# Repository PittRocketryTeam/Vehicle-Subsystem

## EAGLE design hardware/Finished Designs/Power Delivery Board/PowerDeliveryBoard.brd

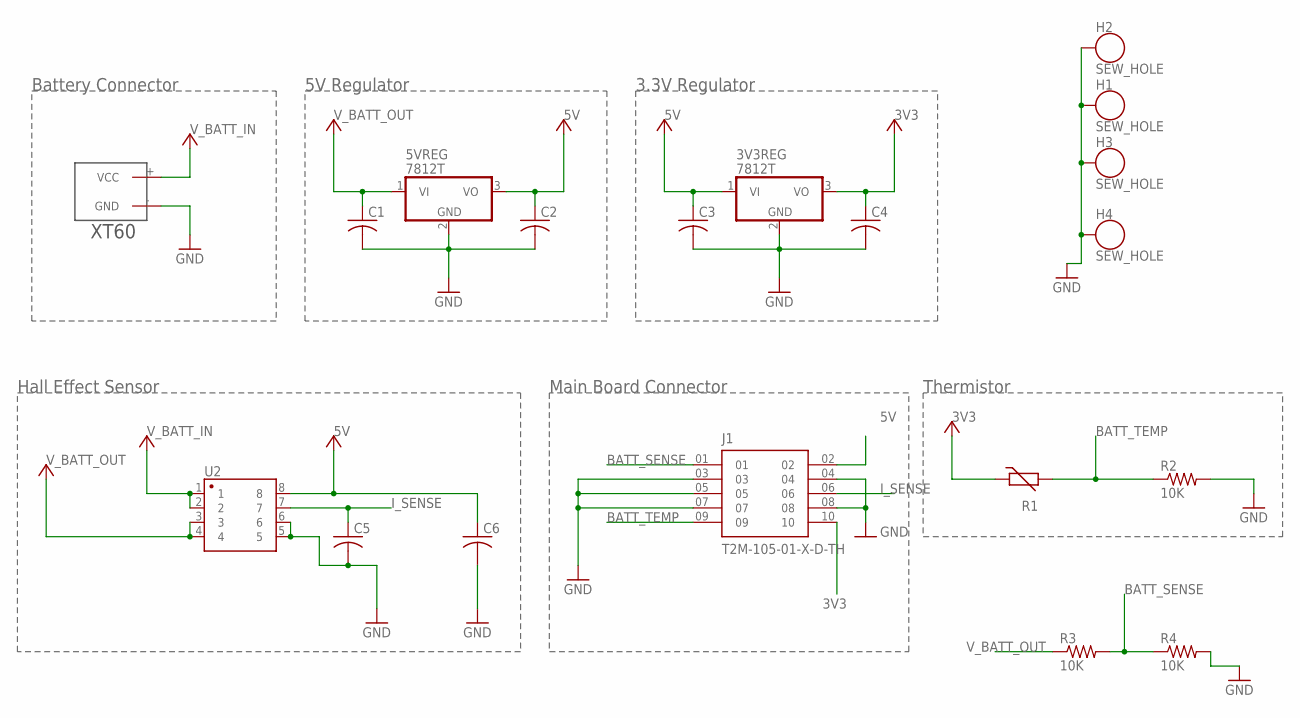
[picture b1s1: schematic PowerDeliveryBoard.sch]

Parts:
3V3REG, 5VREG: 7812T; TO220H
C1, C2, C3, C4, C5, C6: C-USC0805; C0805
H1, H2, H3, H4: SEW_HOLE; SIMPLE_HOLE
J1: T2M-105-01-X-D-TH; SAMTEC_T2M-105-01-X-D-TH
R1: THERMISTOR-5; R-5
R2, R3, R4: 10K; R0805
U2: ASC723; SO08
U$3: XT60_XT60

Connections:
3V3: 3V3REG.3 (VO), C4.1, J1.10, R1.1
5V: 3V3REG.1 (VI), 5VREG.3 (VO), C2.1, C3.1, C6.1, J1.02, U2.8
BATT_SENSE: J1.01, R3.2, R4.1
BATT_TEMP: J1.09, R1.2, R2.1
GND: 3V3REG.2 (GND), 5VREG.2 (GND), C1.2, C2.2, C3.2, C4.2, C5.2, C6.2, H1.P$1, H2.P$1, H3.P$1, H4.P$1, J1.03, J1.04, J1.05, J1.07, J1.08, R2.2, R4.2, U2.5, U2.6, U$3.- (GND)
I_SENSE: C5.1, J1.06, U2.7
V_BATT_IN: U2.1, U2.2, U$3.+ (VCC)
V_BATT_OUT: 5VREG.1 (VI), C1.1, R3.1, U2.3, U2.4

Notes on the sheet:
Hall Effect Sensor
5V Regulator
3.3V Regulator
Thermistor
Battery Connector
Main Board Connector

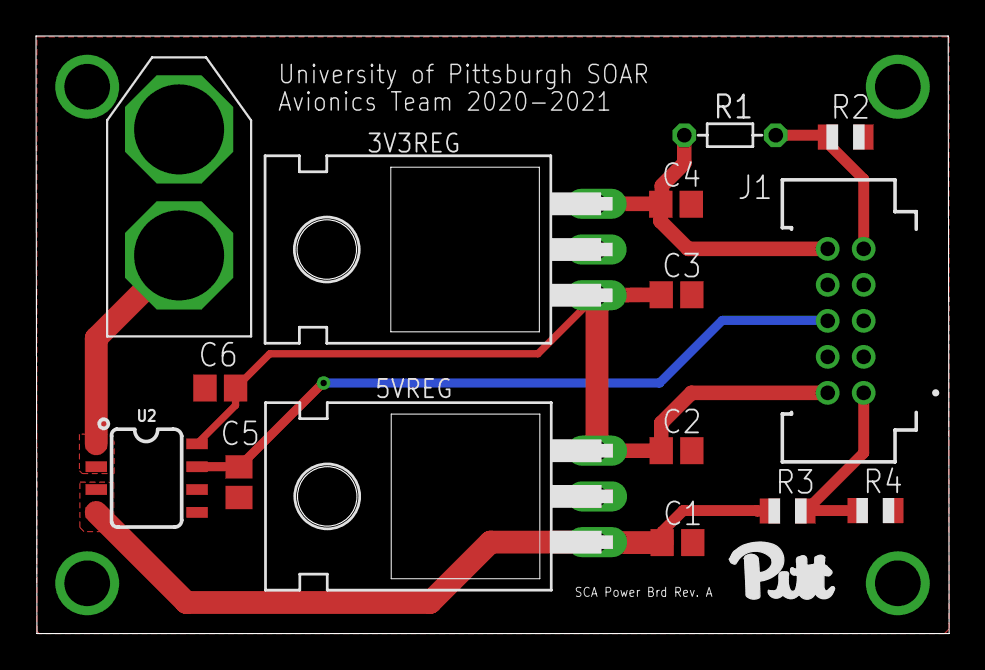
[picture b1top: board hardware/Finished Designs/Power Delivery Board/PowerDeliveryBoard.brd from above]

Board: 2 copper layers, 50.7 x 33.2 mm, 19 parts (0 on the bottom side), 8 nets.

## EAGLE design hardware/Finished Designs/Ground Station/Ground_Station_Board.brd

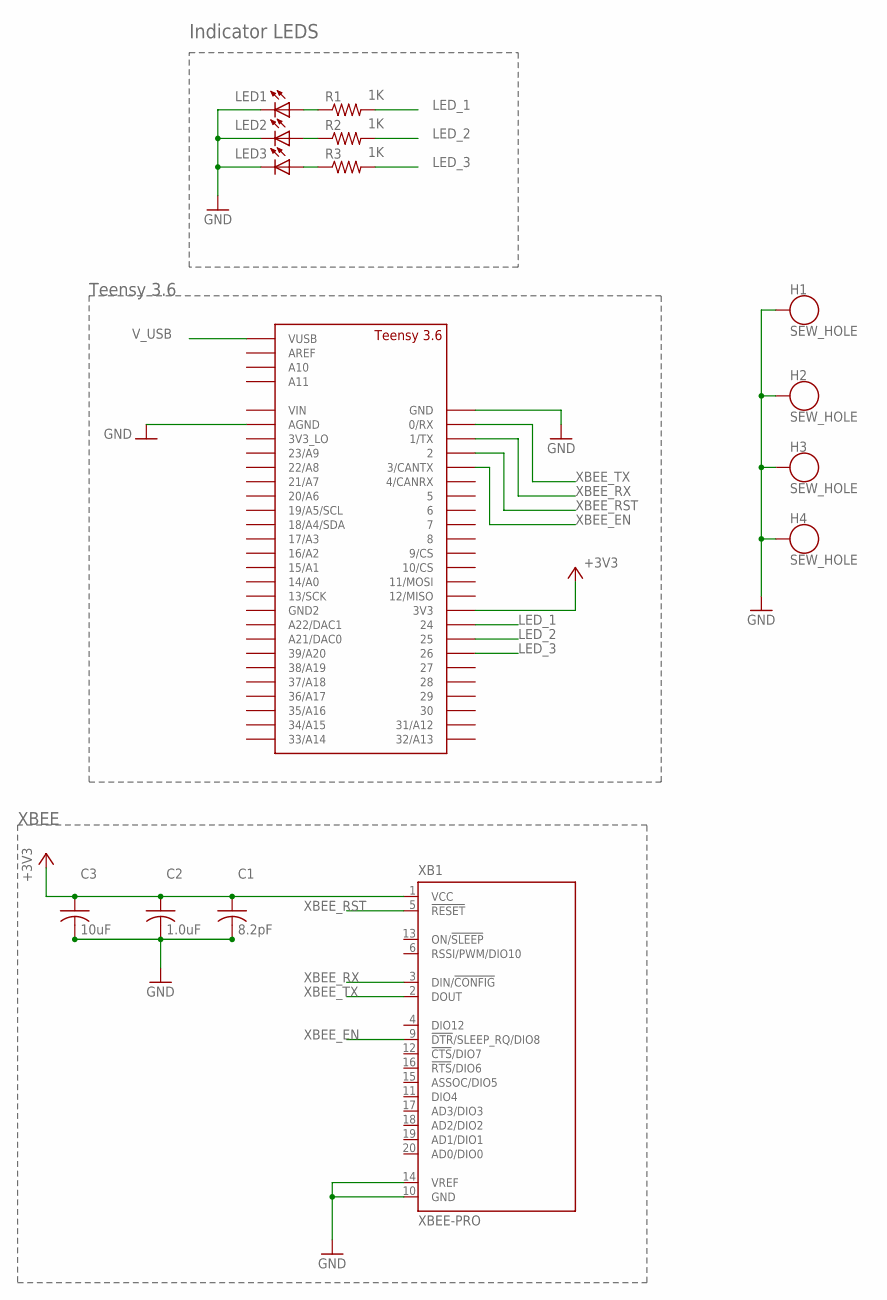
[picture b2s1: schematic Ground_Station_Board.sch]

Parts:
C1: 8.2pF; C025-024X044
C2: 1.0uF; C025-024X044
C3: 10uF; C025-024X044
H1, H2, H3, H4: SEW_HOLE; SIMPLE_HOLE
LED1, LED2, LED3: LED5MM
R1, R2, R3: 1K; 0207/7
U$2: TEENSY_3.5/3.6_BASIC
XB1: XBEE-PRO

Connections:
+3V3: C1.1, C2.1, C3.1, U$2.3V3, XB1.1 (VCC)
GND: C1.2, C2.2, C3.2, H1.P$1, H2.P$1, H3.P$1, H4.P$1, LED1.K (C), LED2.K (C), LED3.K (C), U$2.AGND, U$2.GND, XB1.10 (GND), XB1.14 (VREF)
LED_1: R1.2, U$2.24
LED_2: R2.2, U$2.25
LED_3: R3.2, U$2.26
unnamed: LED1.A, R1.1
unnamed: LED2.A, R2.1
unnamed: LED3.A, R3.1
V_USB: U$2.VUSB
XBEE_EN: U$2.3/CANTX, XB1.9 (!DTR!/SLEEP_RQ/DIO8)
XBEE_RST: U$2.2, XB1.5 (!RESET)
XBEE_RX: U$2.1/TX, XB1.3 (DIN/!CONFIG)
XBEE_TX: U$2.0/RX, XB1.2 (DOUT)

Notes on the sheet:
Indicator LEDS
XBEE
Teensy 3.6

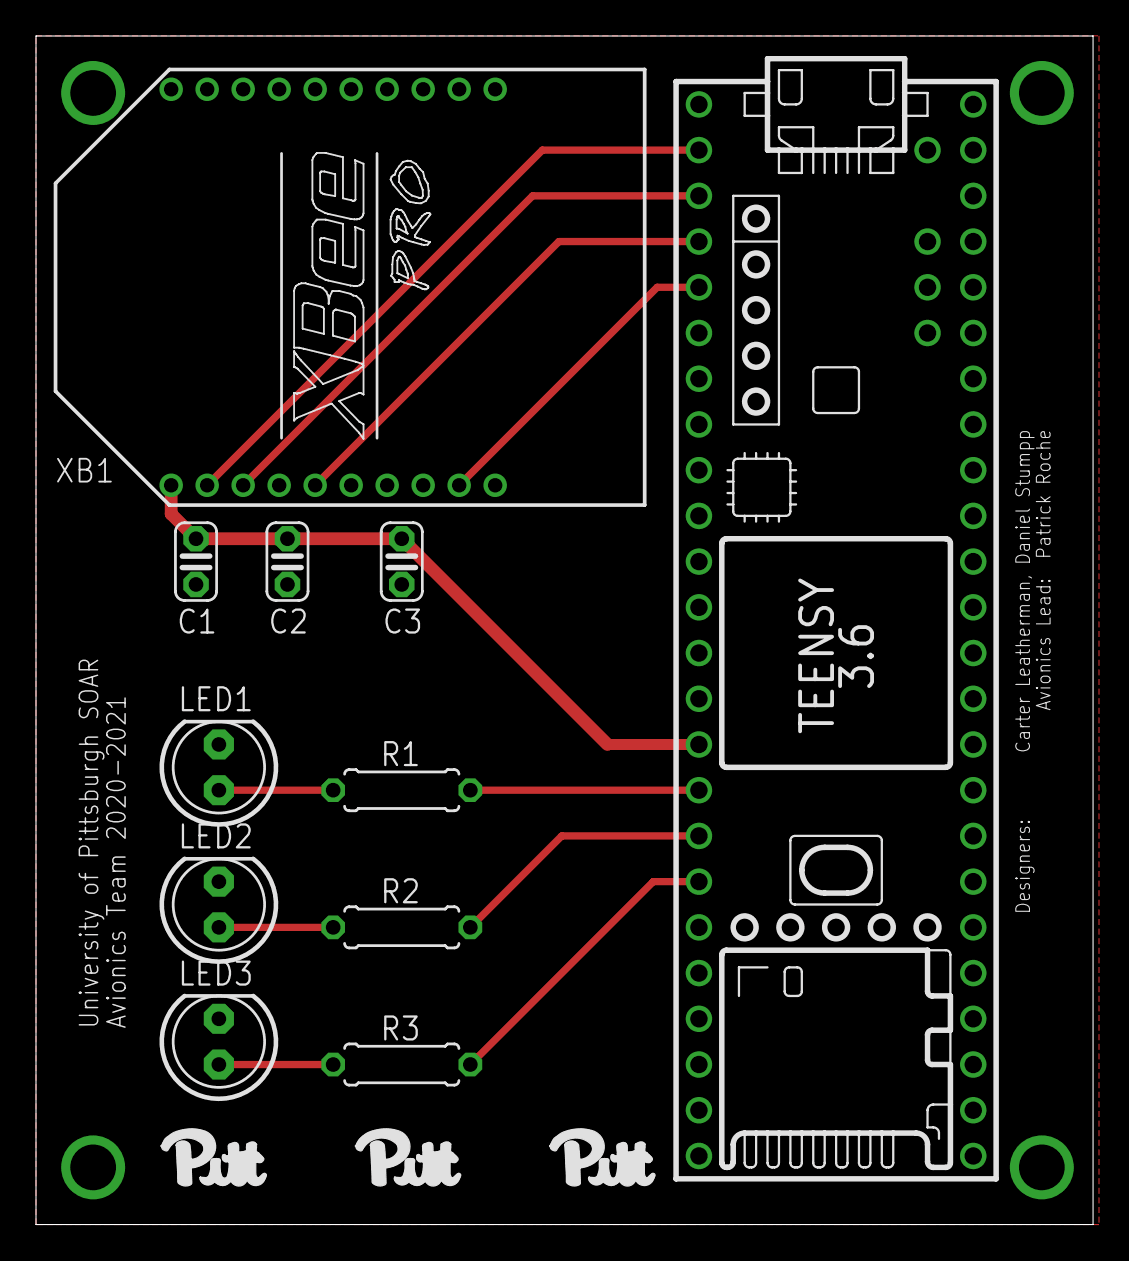
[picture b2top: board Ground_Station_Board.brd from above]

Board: 2 copper layers, 58.7 x 66.0 mm, 15 parts (0 on the bottom side), 12 nets.

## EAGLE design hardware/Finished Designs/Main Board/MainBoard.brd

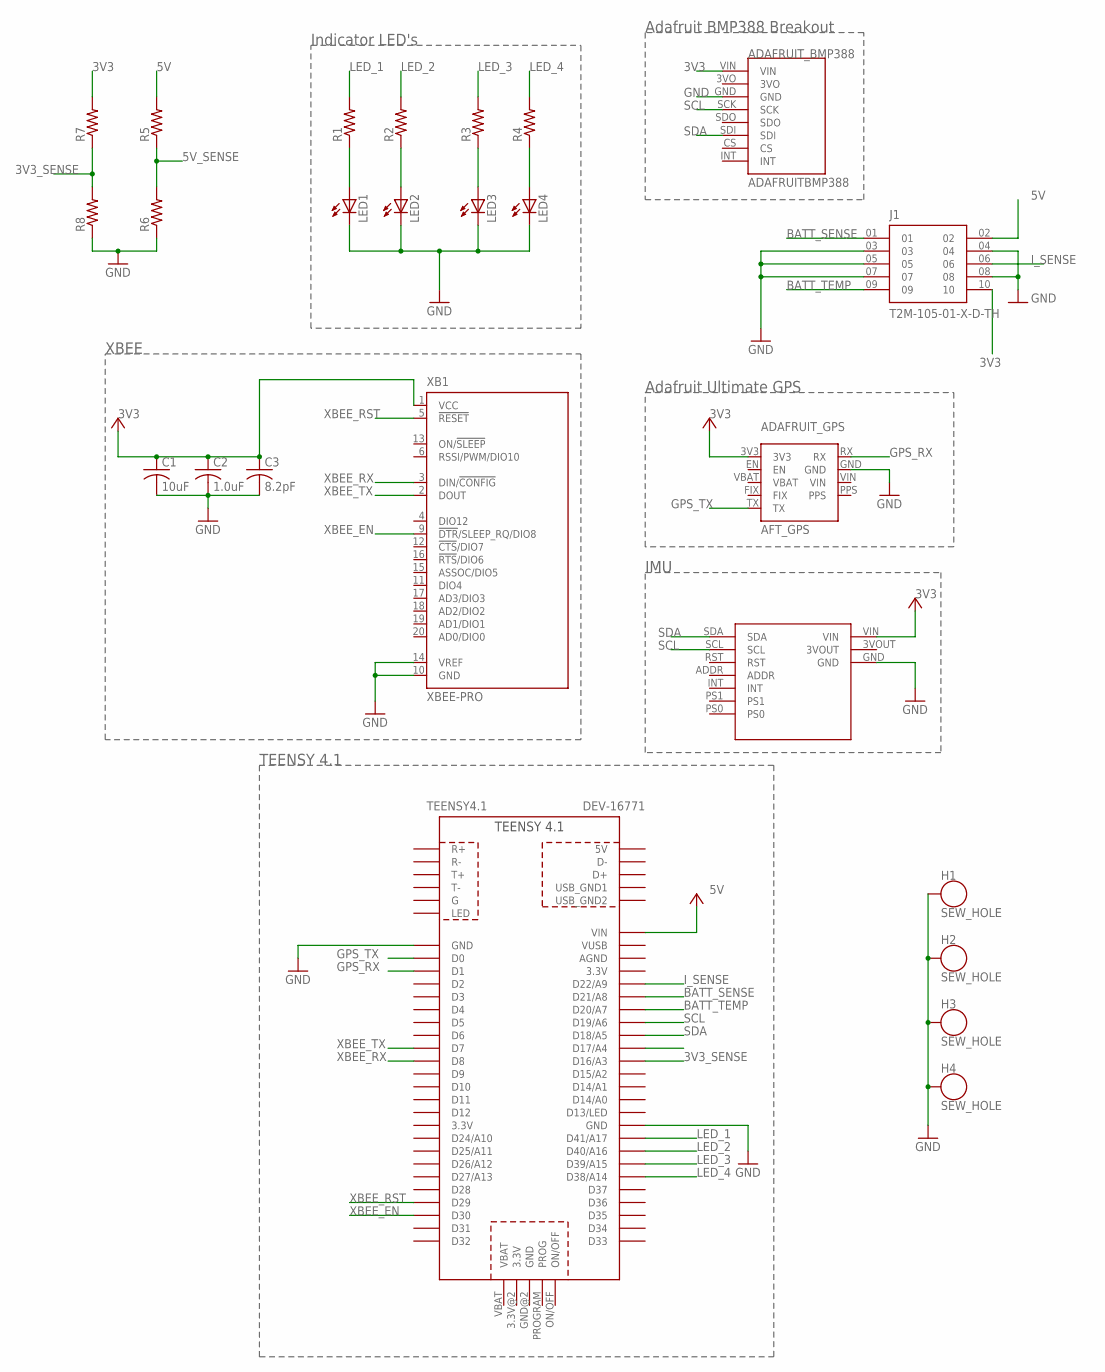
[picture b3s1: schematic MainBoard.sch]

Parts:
ADAFRUIT_BMP388: ADAFRUITBMP388
ADAFRUIT_GPS: AFT_GPS
C1: 10uF; C0805
C2: 1.0uF; C0805
C3: 8.2pF; C0805
H1, H2, H3, H4: SEW_HOLE; SIMPLE_HOLE
J1: T2M-105-01-X-D-TH; SAMTEC_T2M-105-01-X-D-TH
LED1, LED2, LED3, LED4: LED5MM
R1, R2, R3, R4, R5, R6, R7, R8: R-US_R0805; R0805
TEENSY4.1: DEV-16771
U$1: IMU_BREAKOUT; BNO055_BREAKOUT
XB1: XBEE-PRO

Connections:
3.3V: TEENSY4.1.3.3V, TEENSY4.1.3.3V@1 (3.3V), TEENSY4.1.3.3V@2 (3.3V)
3V3: ADAFRUIT_BMP388.VIN, ADAFRUIT_GPS.3V3, C1.1, C2.1, C3.1, J1.10, R7.2, U$1.VIN, XB1.1 (VCC)
3V3_SENSE: R7.1, R8.2, TEENSY4.1.D17/A3 (D16/A3)
5V: J1.02, R5.2, TEENSY4.1.5V, TEENSY4.1.VIN
5V_SENSE: R5.1, R6.2, TEENSY4.1.D18/A4 (D17/A4)
AGND: TEENSY4.1.AGND
BATT_SENSE: J1.01, TEENSY4.1.D22/A8 (D21/A8)
BATT_TEMP: J1.09, TEENSY4.1.D21/A7 (D20/A7)
G: TEENSY4.1.G
GND: ADAFRUIT_BMP388.GND, ADAFRUIT_GPS.GND, C1.2, C2.2, C3.2, H1.P$1, H2.P$1, H3.P$1, H4.P$1, J1.03, J1.04, J1.05, J1.07, J1.08, LED1.K (C), LED2.K (C), LED3.K (C), LED4.K (C), R6.1, R8.1, TEENSY4.1.GND, TEENSY4.1.GND@1 (GND), TEENSY4.1.GND@2 (GND), U$1.GND, XB1.10 (GND), XB1.14 (VREF)
GPS_RX: ADAFRUIT_GPS.RX, TEENSY4.1.D1
GPS_TX: ADAFRUIT_GPS.TX, TEENSY4.1.D0
I_SENSE: J1.06, TEENSY4.1.D23/A9 (D22/A9)
LED_1: R1.2, TEENSY4.1.D41/A17
LED_2: R2.2, TEENSY4.1.D40/A16
LED_3: R3.2, TEENSY4.1.D39/A15
LED_4: R4.2, TEENSY4.1.D38/A14
unnamed: LED1.A, R1.1
unnamed: LED2.A, R2.1
unnamed: LED3.A, R3.1
unnamed: LED4.A, R4.1
SCL: ADAFRUIT_BMP388.SCK, TEENSY4.1.D20/A6 (D19/A6), U$1.SCL
SDA: ADAFRUIT_BMP388.SDI, TEENSY4.1.D19/A5 (D18/A5), U$1.SDA
USB_GND1: TEENSY4.1.USB_GND (USB_GND1)
USB_GND2: TEENSY4.1.USB_GND@2 (USB_GND2)
VBAT: TEENSY4.1.VBAT
VUSB: TEENSY4.1.VUSB
XBEE_EN: TEENSY4.1.D30, XB1.9 (!DTR!/SLEEP_RQ/DIO8)
XBEE_RST: TEENSY4.1.D29, XB1.5 (!RESET)
XBEE_RX: TEENSY4.1.D8, XB1.3 (DIN/!CONFIG)
XBEE_TX: TEENSY4.1.D7, XB1.2 (DOUT)

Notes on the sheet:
Indicator LED's
Adafruit Ultimate GPS
XBEE
TEENSY 4.1
IMU
Adafruit BMP388 Breakout

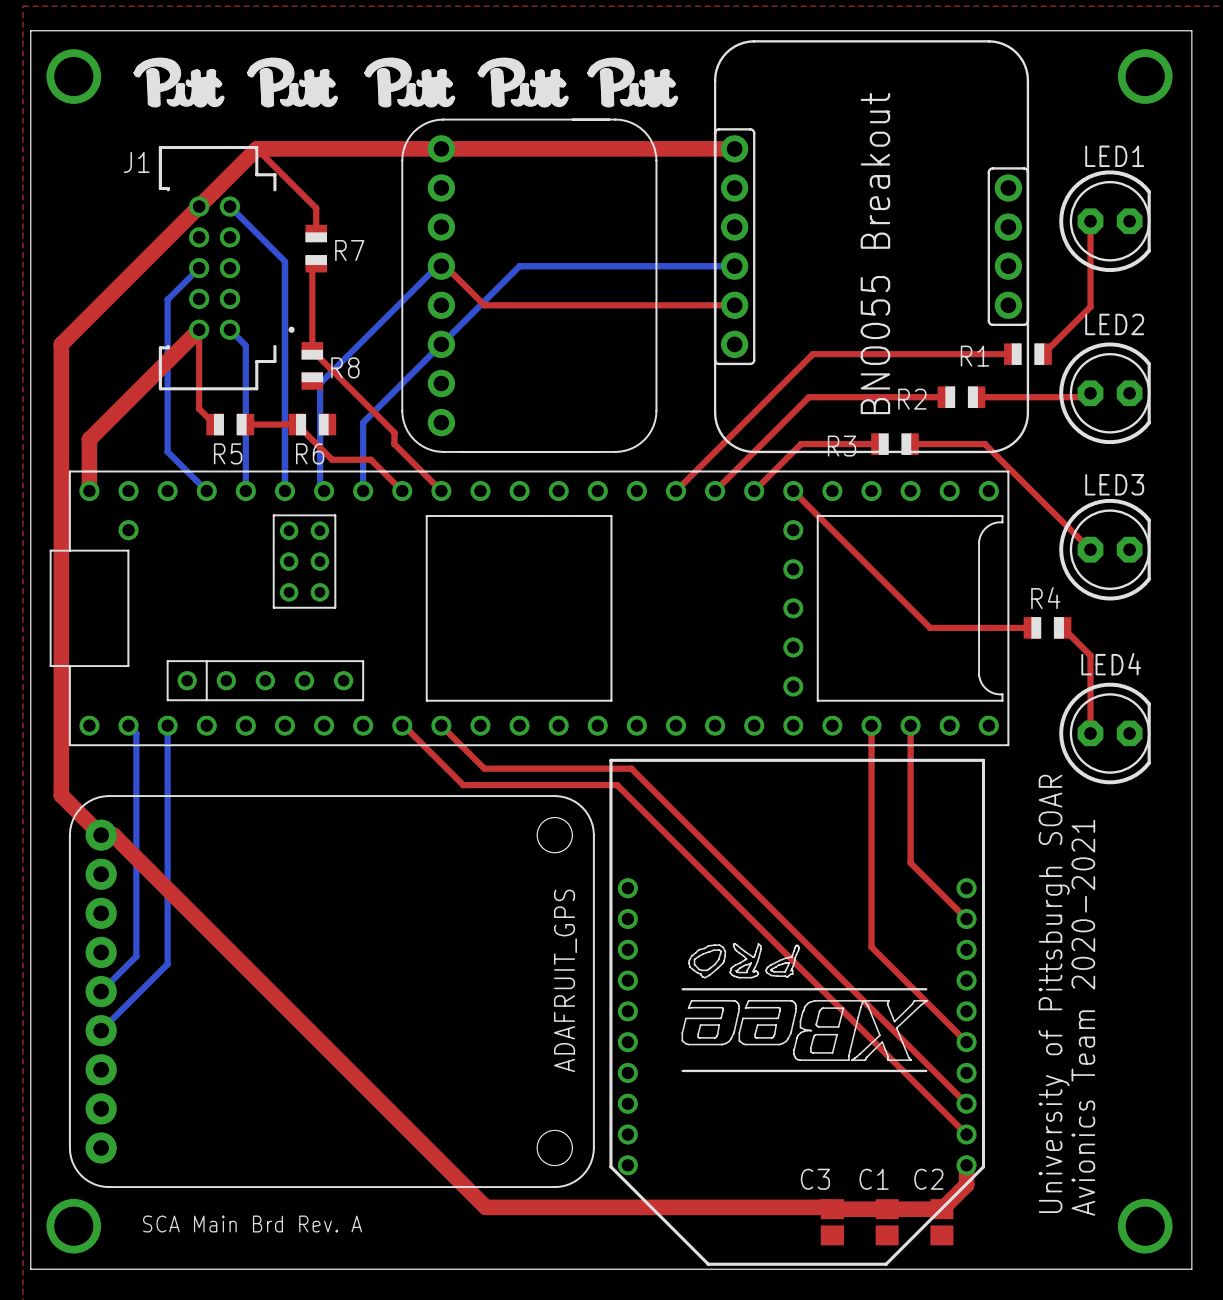
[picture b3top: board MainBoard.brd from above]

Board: 2 copper layers, 75.4 x 80.4 mm, 25 parts (0 on the bottom side), 25 nets.

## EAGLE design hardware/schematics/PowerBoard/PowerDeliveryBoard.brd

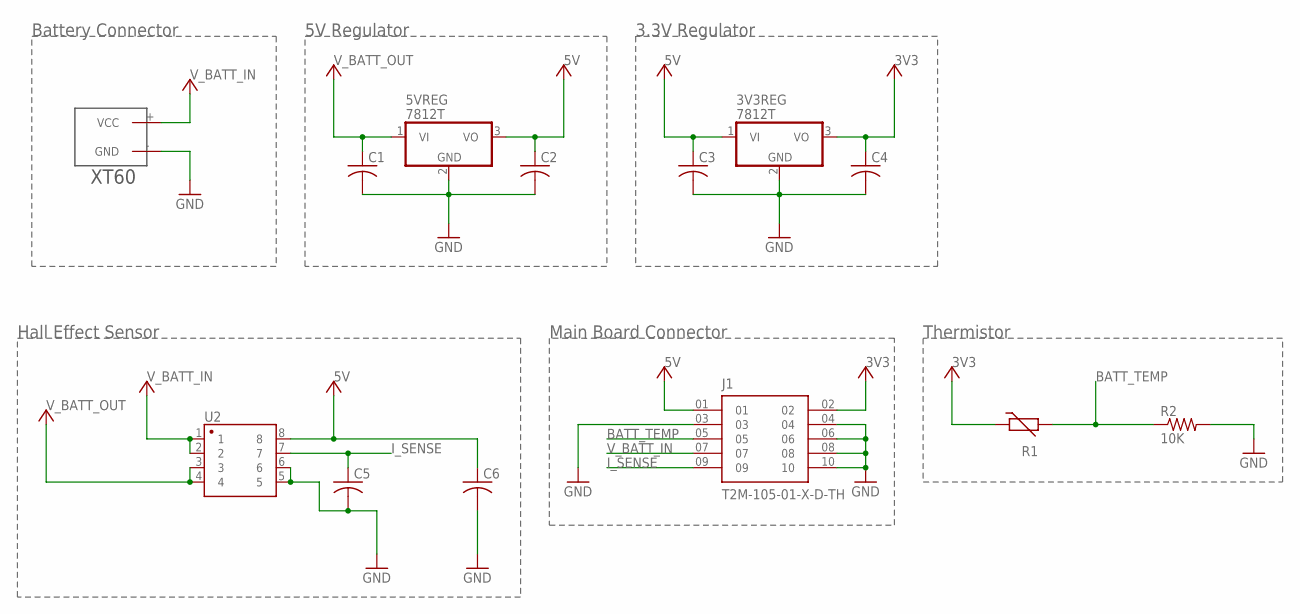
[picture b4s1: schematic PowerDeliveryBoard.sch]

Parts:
3V3REG, 5VREG: 7812T; TO220H
C1, C2, C3, C4, C5, C6: C-USC0805; C0805
J1: T2M-105-01-X-D-TH; SAMTEC_T2M-105-01-X-D-TH
R1: THERMISTOR-5; R-5
R2: 10K; R0805
U2: ASC723; SO08
U$3: XT60_XT60

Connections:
3V3: 3V3REG.3 (VO), C4.1, J1.02, R1.1
5V: 3V3REG.1 (VI), 5VREG.3 (VO), C2.1, C3.1, C6.1, J1.01, U2.8
BATT_TEMP: J1.05, R1.2, R2.1
GND: 3V3REG.2 (GND), 5VREG.2 (GND), C1.2, C2.2, C3.2, C4.2, C5.2, C6.2, J1.03, J1.04, J1.06, J1.08, J1.10, R2.2, U2.5, U2.6, U$3.- (GND)
I_SENSE: C5.1, J1.09, U2.7
V_BATT_IN: J1.07, U2.1, U2.2, U$3.+ (VCC)
V_BATT_OUT: 5VREG.1 (VI), C1.1, U2.3, U2.4

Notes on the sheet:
Hall Effect Sensor
5V Regulator
3.3V Regulator
Thermistor
Battery Connector
Main Board Connector

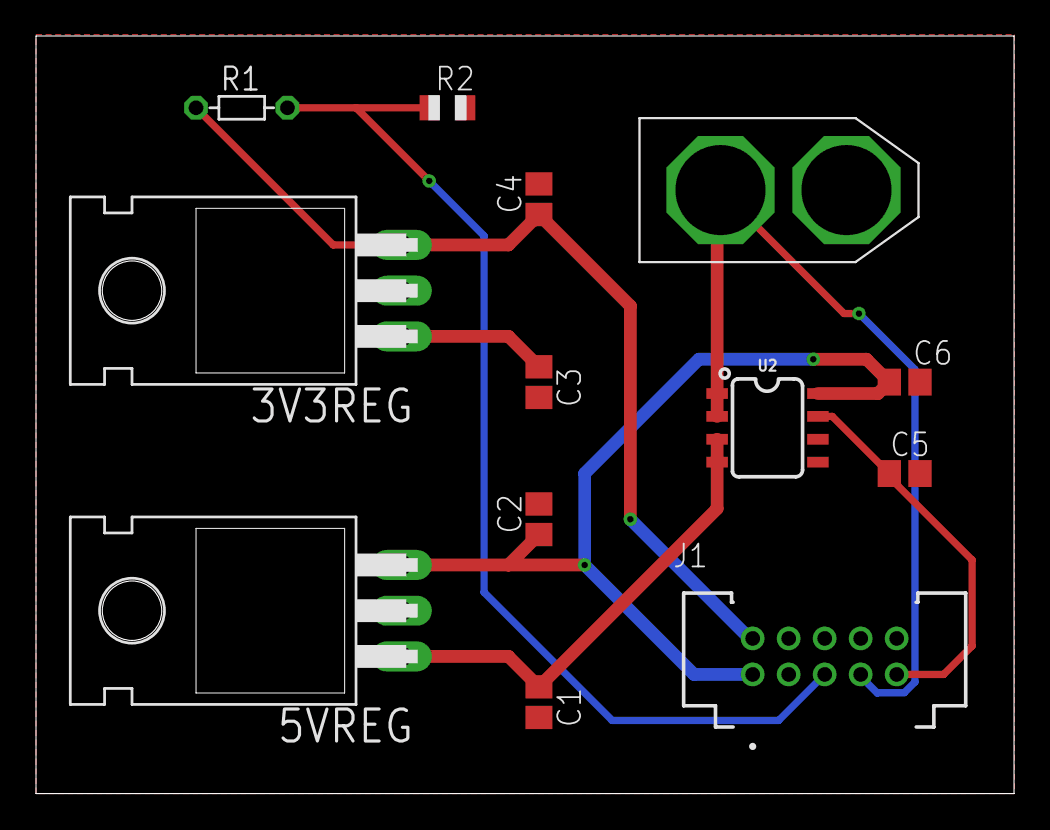
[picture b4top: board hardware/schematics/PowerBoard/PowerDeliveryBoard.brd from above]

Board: 2 copper layers, 54.3 x 42.1 mm, 13 parts (0 on the bottom side), 7 nets.

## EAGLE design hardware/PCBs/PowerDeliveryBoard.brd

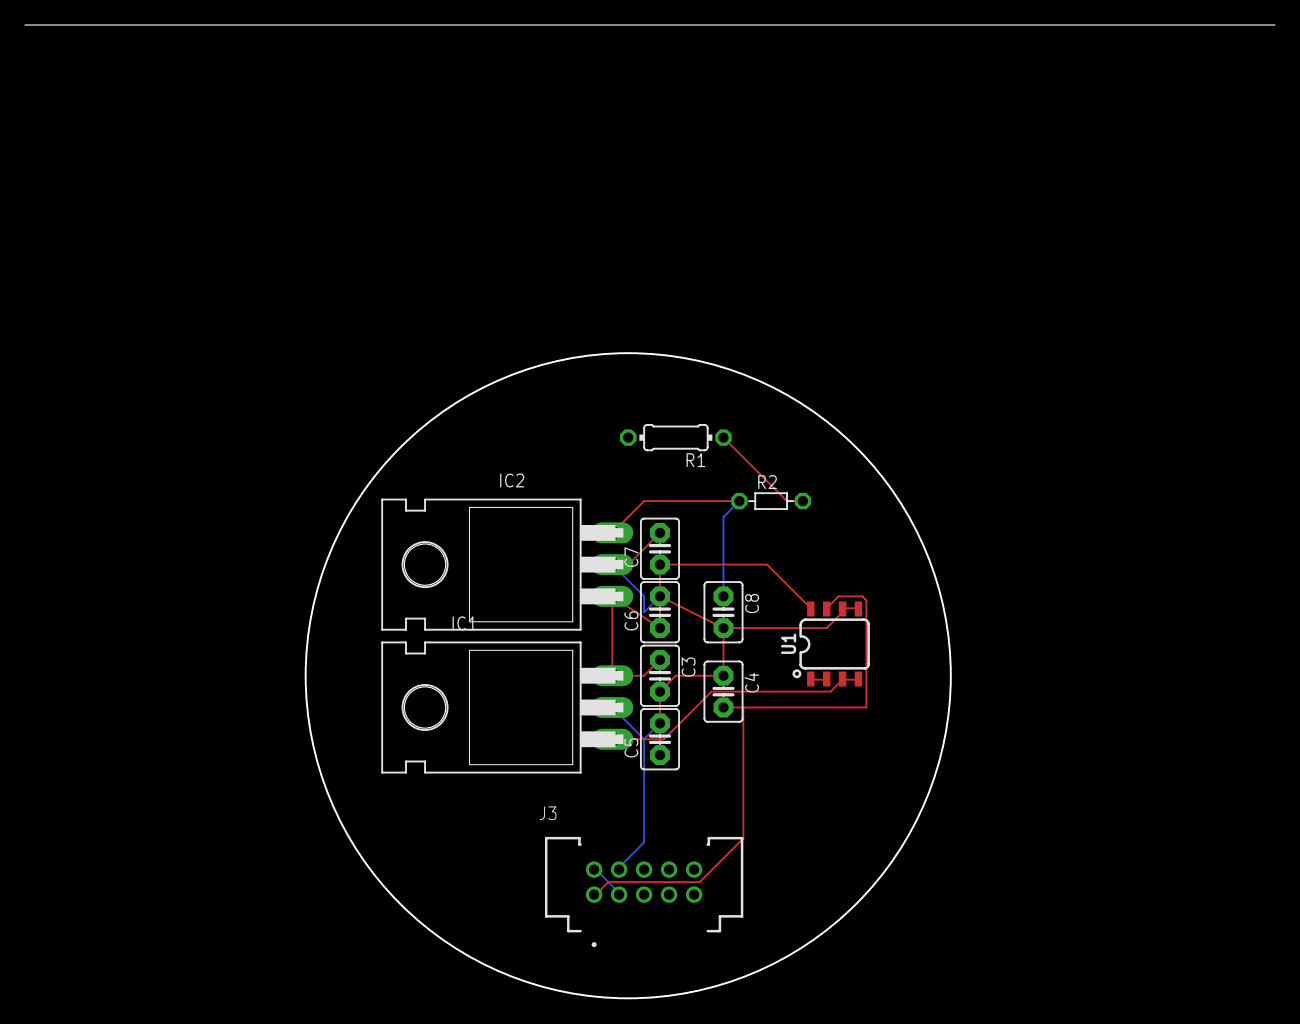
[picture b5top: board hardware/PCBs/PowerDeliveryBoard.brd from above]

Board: 2 copper layers, 51.6 x 51.6 mm, 12 parts (0 on the bottom side), 8 nets.

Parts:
C3: .1 uF; C2.5-3
C4: C2.5-3
C5, C7: 1uF; C2.5-3
C6, C8: .1uF; C2.5-3
IC1, IC2: 7812T; TO220H
J3: T2M-105-01-X-D-TH; SAMTEC_T2M-105-01-X-D-TH
R1: 0; 0204/7
R2: THERMISTOR-5; R-5
U1: GENERIC-SOIC8MSGEQ7N-FILTER; SO08

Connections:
+3V3: C8.1, IC2.3, R2.1
+5V: C3.1, C6.1, C7.1, IC1.3, IC2.1, U1.8
GND: C3.2, C4.1, C5.2, C6.2, C7.2, C8.2, IC1.2, IC2.2, J3.04, U1.5, U1.6
unnamed: R1.1, R2.2
VCC: J3.02, J3.03
VI_OUT: C4.2, J3.01, U1.7
V_BATT: C5.1, IC1.1, U1.3, U1.4
V_BATT_IN: U1.1, U1.2

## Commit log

2020-10-25 Delete Ground_Station_Board.sch
    Wrong folder
2020-11-01 changes from review
2020-11-01 power
2020-12-11 Add files via upload
    Updated resistor and capacitor values
2020-12-14 upload
2020-12-17 RF_Board upload
2020-12-17 Everything in one folder
2020-12-17 PDFs
2020-12-17 getting rid of # files
2020-12-17 Add comment
2020-12-17 board's smaller now
2020-12-17 Wider power trace
2020-12-22 .sch+.brd of Main Board | still needs altimeter
2020-12-27 Added BMP388 & PDF's
2020-12-27 Added render image
2020-12-27 Update PDF
2020-12-29 Updates
    Made power traces wider
    Added XBEE enable and reset traces
    Moved I2C pins to correct pins on teensy
    Made caps 805 size
2020-12-29 Deleting .b#3 file
2020-12-29 Added top layer ground pour
2020-12-30 Fixed TX/RX pins for GPS and Xbee
2020-12-31 Changed Xbee -> Xbee-Pro | Added render png
2021-01-21 MainBoard Power routing & Power Board PNG
2021-01-22 burn the evidence
2021-01-22 libraries
2021-01-22 Add Power Board | Change MB Connector Pins | Move Old PDB.sch to PCBs Folder
2021-01-23 logger is now working
2021-01-23 add hw timers
2021-01-24 Uploading Finalized Ground Station and Main Board
2021-01-24 Uploading finalized power board
2021-02-06 everything is broken
2021-02-10 latest
2021-02-10 Come, sweet death.
2021-02-12 more work
2021-02-12 fix imu addr
2021-02-13 the gps FINALLY works, but I broke the IMU
2021-02-14 work on health class
2021-03-12 untested changes :(
2021-03-13 tweaks
2021-03-26 clean some stuff up
2021-04-16 start on payload deploy algorithm

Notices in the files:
parts and their libraries:
SparkFun-Retired: Licensing: Creative Commons ShareAlike 4.0 International - https://creativecommons.org/licenses/by-sa/4.0
